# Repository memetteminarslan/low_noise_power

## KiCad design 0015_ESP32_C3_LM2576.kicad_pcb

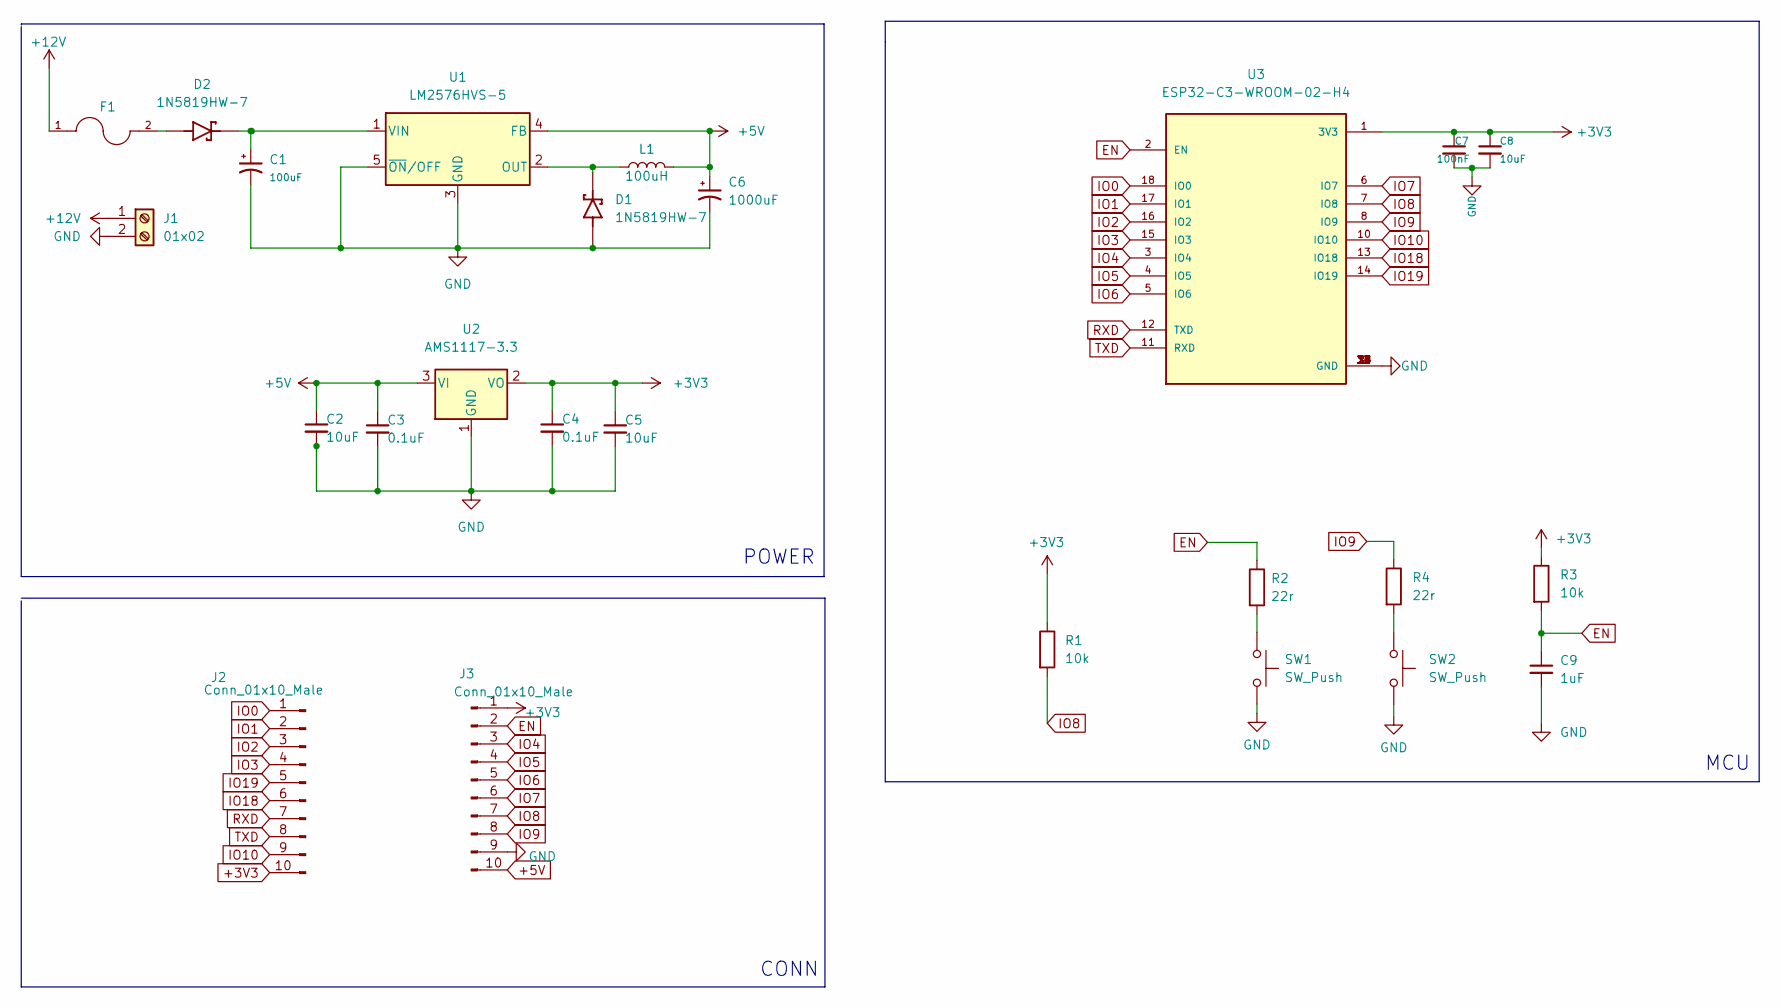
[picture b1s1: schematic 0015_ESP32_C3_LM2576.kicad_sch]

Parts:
C1: 100uF; CP_Elec_6.3x7.7
C2, C5, C8: 10uF; C_0805_2012Metric
C3, C4: 0.1uF; C_0805_2012Metric
C6: 1000uF; CP_Elec_10x12.6
C7: 100nF; C_0805_2012Metric
C9: 1uF; C_0805_2012Metric
D1, D2: 1N5819HW-7; SOD3715X145N; PARTREV 18-2
F1: 0685T8000-01; FUSC3215X83N; PARTREV Jan2019
J1: 01x02; TerminalBlock_bornier-2_P5.08mm
J2, J3: Conn_01x10_Male; PinHeader_1x10_P2.54mm_Vertical
L1: 100uH
R1, R3: 10k; R_0805_2012Metric
R2, R4: 22r; R_0805_2012Metric
SW1, SW2: SW_Push; SW_TL1015AF160QG
U1: LM2576HVS-5; TO-263-5_TabPin3
U2: AMS1117-3.3; SOT-223-3_TabPin2
U3: ESP32-C3-WROOM-02-H4; MODULE_ESP32-C3-WROOM-02-H4

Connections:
+3V3: C4.1, C5.1, C7.1, C8.1, J2.10, J3.1, R1.1, R3.1, U2.2 (VO), U3.1 (3V3)
+5V: C2.1, C3.1, C6.1, J3.10, L1.2, U1.4 (FB), U2.3 (VI)
+12V: F1.1, J1.1
EN: C9.1, J3.2, R2.1, R3.2, U3.2 (EN)
GND: C1.2, C2.2, C3.2, C4.2, C5.2, C6.2, C7.2, C8.2, C9.2, D1.A, J1.2, J3.9, SW1.2, SW2.2, U1.3 (GND), U1.5 (~ON/OFF), U2.1 (GND), U3.9 (GND), U3.19 (GND), U3.20 (GND), U3.21 (GND), U3.22 (GND), U3.23 (GND), U3.24 (GND), U3.25 (GND), U3.26 (GND), U3.27 (GND), U3.28 (GND), U3.29 (GND), U3.30 (GND), U3.31 (GND), U3.32 (GND), U3.33 (GND), U3.34 (GND), U3.35 (GND), U3.36 (GND), U3.37 (GND), U3.38 (GND), U3.39 (GND)
IO0: J2.1, U3.18 (IO0)
IO1: J2.2, U3.17 (IO1)
IO2: J2.3, U3.16 (IO2)
IO3: J2.4, U3.15 (IO3)
IO4: J3.3, U3.3 (IO4)
IO5: J3.4, U3.4 (IO5)
IO6: J3.5, U3.5 (IO6)
IO7: J3.6, U3.6 (IO7)
IO8: J3.7, R1.2, U3.7 (IO8)
IO9: J3.8, R4.1, U3.8 (IO9)
IO10: J2.9, U3.10 (IO10)
IO18: J2.6, U3.13 (IO18)
IO19: J2.5, U3.14 (IO19)
unnamed: C1.1, D2.C, U1.1 (VIN)
unnamed: D1.C, L1.1, U1.2 (OUT)
unnamed: D2.A, F1.2
unnamed: R2.2, SW1.1
unnamed: R4.2, SW2.1
RXD: J2.7, U3.12 (TXD)
TXD: J2.8, U3.11 (RXD)

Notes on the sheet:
CONN
MCU
POWER

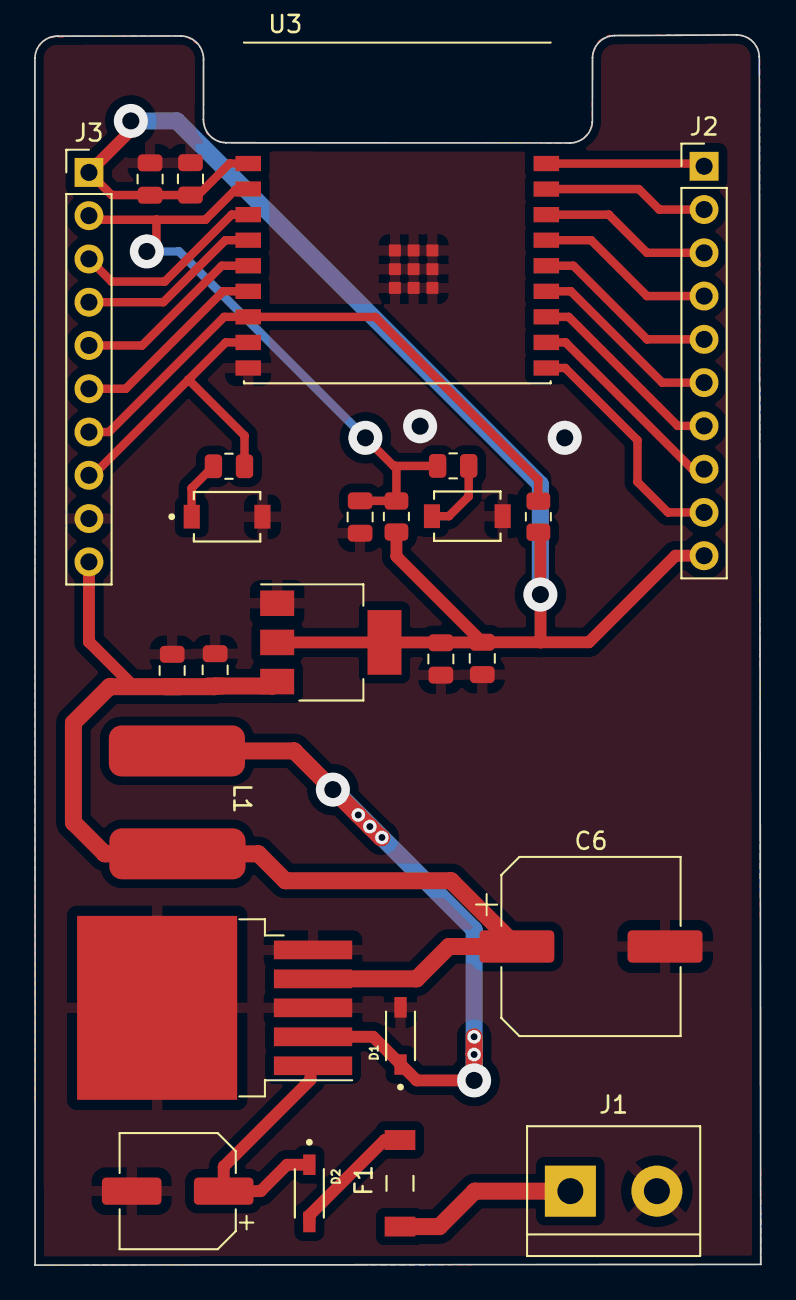
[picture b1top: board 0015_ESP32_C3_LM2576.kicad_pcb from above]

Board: 2 copper layers, 42.6 x 72.2 mm, 25 parts (0 on the bottom side), 25 nets.

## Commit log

2023-03-14 esp32_c3
2023-03-14 esp32 c3 lm2576
    Youtube kanalımda yayınladığım ilk video
